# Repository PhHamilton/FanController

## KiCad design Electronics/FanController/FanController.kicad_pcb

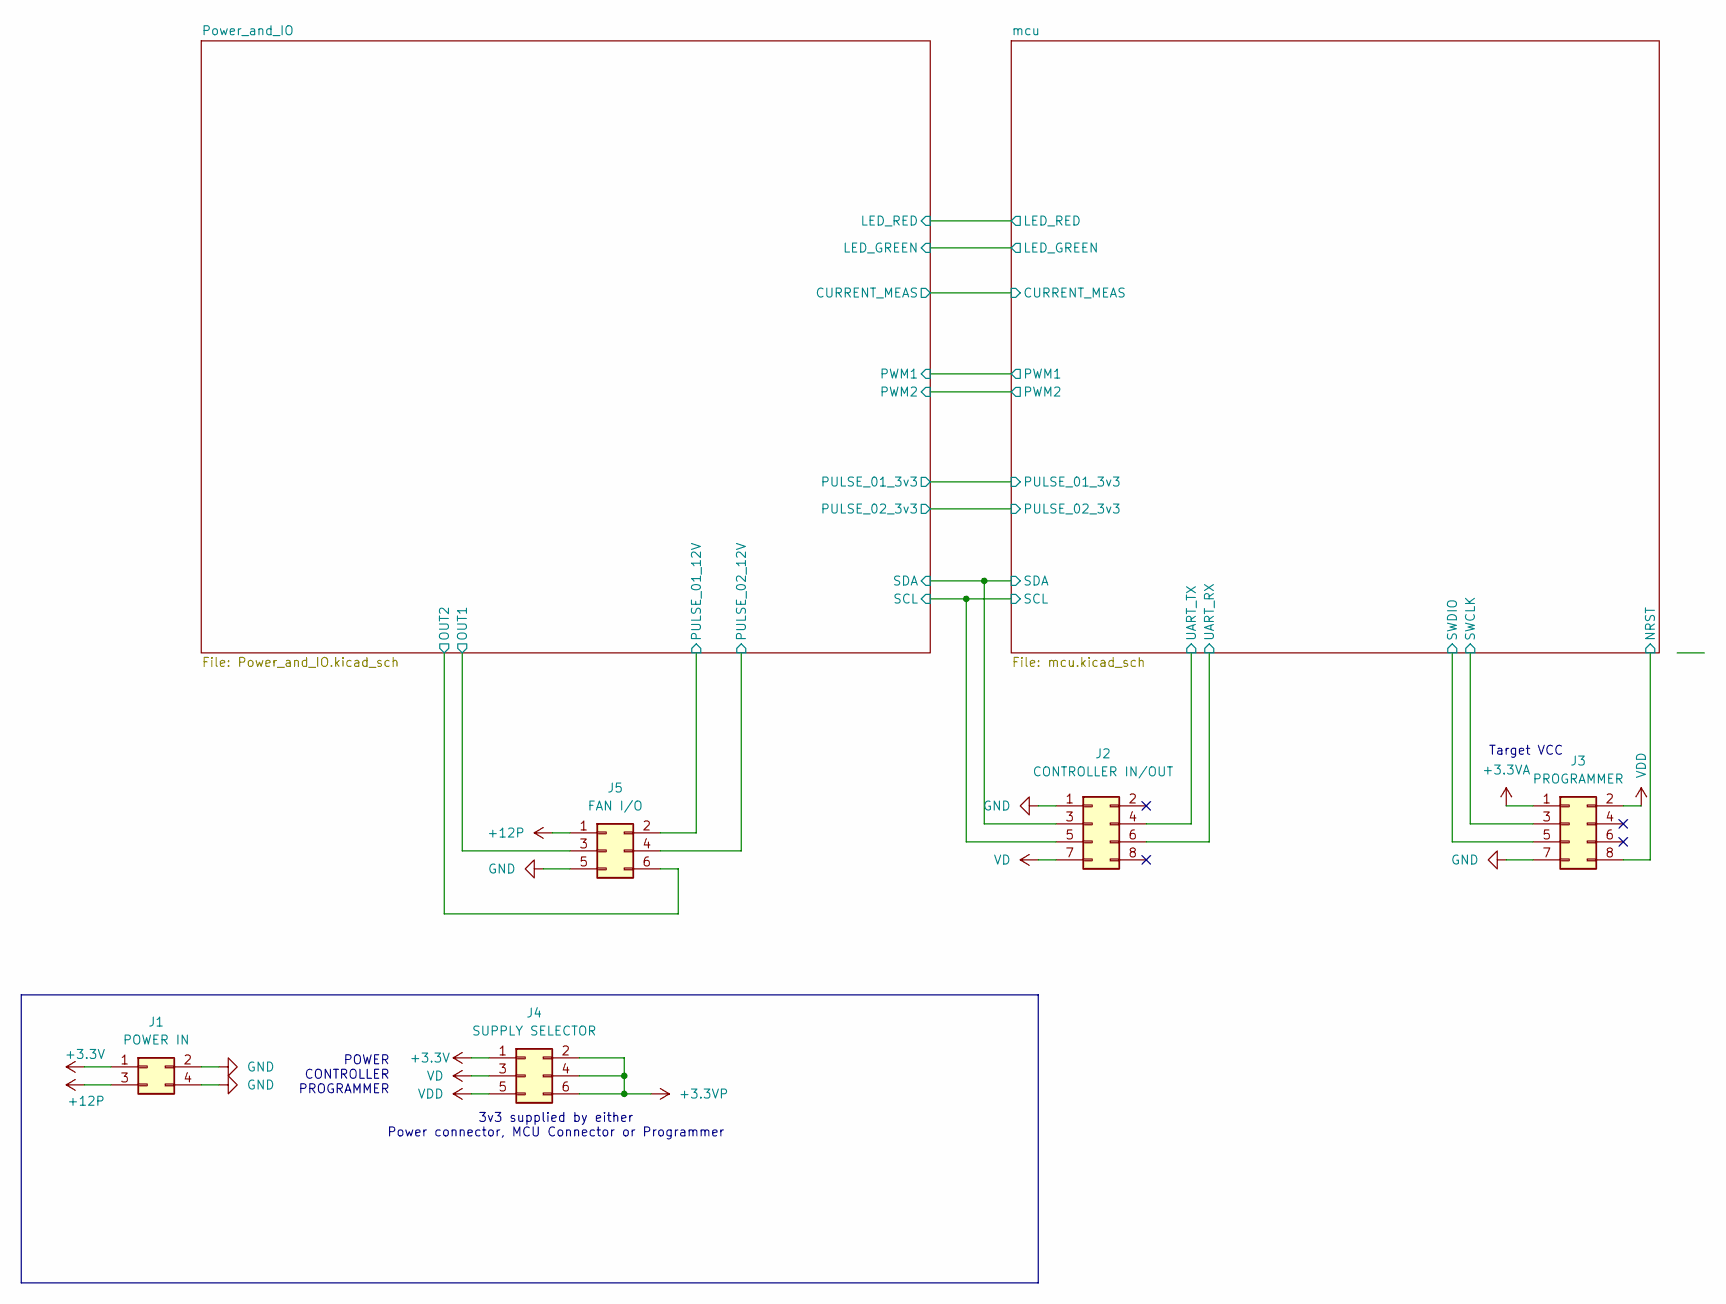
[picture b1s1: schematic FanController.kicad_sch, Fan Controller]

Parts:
J1: POWER IN; PinHeader_2x02_P2.54mm_Horizontal
J2: CONTROLLER IN/OUT; PinHeader_2x04_P2.54mm_Horizontal
J3: PROGRAMMER; PinHeader_2x04_P2.54mm_Vertical
J4: SUPPLY SELECTOR; PinHeader_2x03_P2.54mm_Vertical
J5: FAN I/O; PinHeader_2x03_P2.54mm_Horizontal

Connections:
+3.3V: J1.1, J4.1
+3.3VA: J3.1
+3.3VP: J4.2, J4.4, J4.6; also elsewhere on the board
+12P: J1.3, J5.1; also elsewhere on the board
/Power_and_IO/OUT1: J5.3; also elsewhere on the board
/Power_and_IO/OUT2: J5.6; also elsewhere on the board
/Power_and_IO/PULSE_01_12V: J5.2; also elsewhere on the board
/Power_and_IO/PULSE_02_12V: J5.4; also elsewhere on the board
/Power_and_IO/SCL: J2.5; also elsewhere on the board
/Power_and_IO/SDA: J2.3; also elsewhere on the board
/mcu/NRST: J3.8; also elsewhere on the board
/mcu/SWCLK: J3.3; also elsewhere on the board
/mcu/SWDIO: J3.5; also elsewhere on the board
/mcu/UART_RX: J2.6; also elsewhere on the board
/mcu/UART_TX: J2.4; also elsewhere on the board
GND: J1.2, J1.4, J2.1, J3.7, J5.5; also elsewhere on the board
VD: J2.7, J4.3
VDD: J3.2, J4.5

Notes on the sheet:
3v3 supplied by either Power connector, MCU Connector or Programmer
Target VCC
POWER CONTROLLER PROGRAMMER

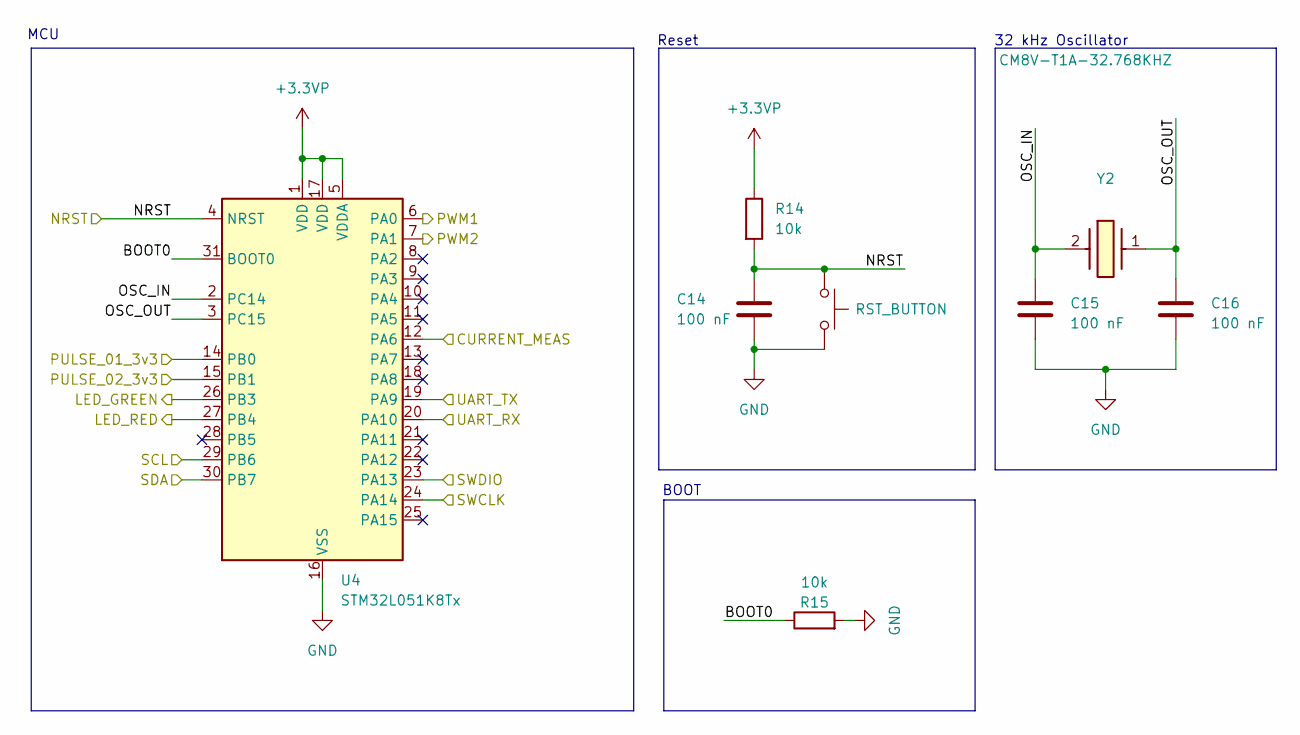
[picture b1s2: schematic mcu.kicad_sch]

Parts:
C14, C15, C16: 100 nF; C_1206_3216Metric_Pad1.33x1.80mm_HandSolder
R14, R15: 10k; R_1206_3216Metric_Pad1.30x1.75mm_HandSolder
SW1: RST_BUTTON; SW_Push_1P1T-SH_NO_CK_KMR2xxG
U4: STM32L051K8Tx; LQFP-32_7x7mm_P0.8mm
Y2: CM8V-T1A-32.768KHZ; Crystal_SMD_MicroCrystal_CC8V-T1A-2Pin_2.0x1.2mm_HandSolder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; Mouser Part Number 428-201494-MC01

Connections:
+3.3VP: R14.1, U4.1 (VDD), U4.5 (VDDA), U4.17 (VDD); also elsewhere on the board
/Power_and_IO/CURRENT_MEAS: U4.12 (PA6); also elsewhere on the board
/Power_and_IO/LED_GREEN: U4.26 (PB3); also elsewhere on the board
/Power_and_IO/LED_RED: U4.27 (PB4); also elsewhere on the board
/Power_and_IO/PULSE_01_3v3: U4.14 (PB0); also elsewhere on the board
/Power_and_IO/PULSE_02_3v3: U4.15 (PB1); also elsewhere on the board
/Power_and_IO/PWM1: U4.6 (PA0); also elsewhere on the board
/Power_and_IO/PWM2: U4.7 (PA1); also elsewhere on the board
/Power_and_IO/SCL: U4.29 (PB6); also elsewhere on the board
/Power_and_IO/SDA: U4.30 (PB7); also elsewhere on the board
/mcu/BOOT0: R15.1, U4.31 (BOOT0)
/mcu/NRST: C14.1, R14.2, SW1.1, U4.4 (NRST); also elsewhere on the board
/mcu/OSC_IN: C15.1, U4.2 (PC14), Y2.2 (X2)
/mcu/OSC_OUT: C16.1, U4.3 (PC15), Y2.1 (X1)
/mcu/SWCLK: U4.24 (PA14); also elsewhere on the board
/mcu/SWDIO: U4.23 (PA13); also elsewhere on the board
/mcu/UART_RX: U4.20 (PA10); also elsewhere on the board
/mcu/UART_TX: U4.19 (PA9); also elsewhere on the board
GND: C14.2, C15.2, C16.2, R15.2, SW1.2, U4.16 (VSS), U4.32 (VSS); also elsewhere on the board

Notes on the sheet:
32 kHz Oscillator
MCU
BOOT
Reset

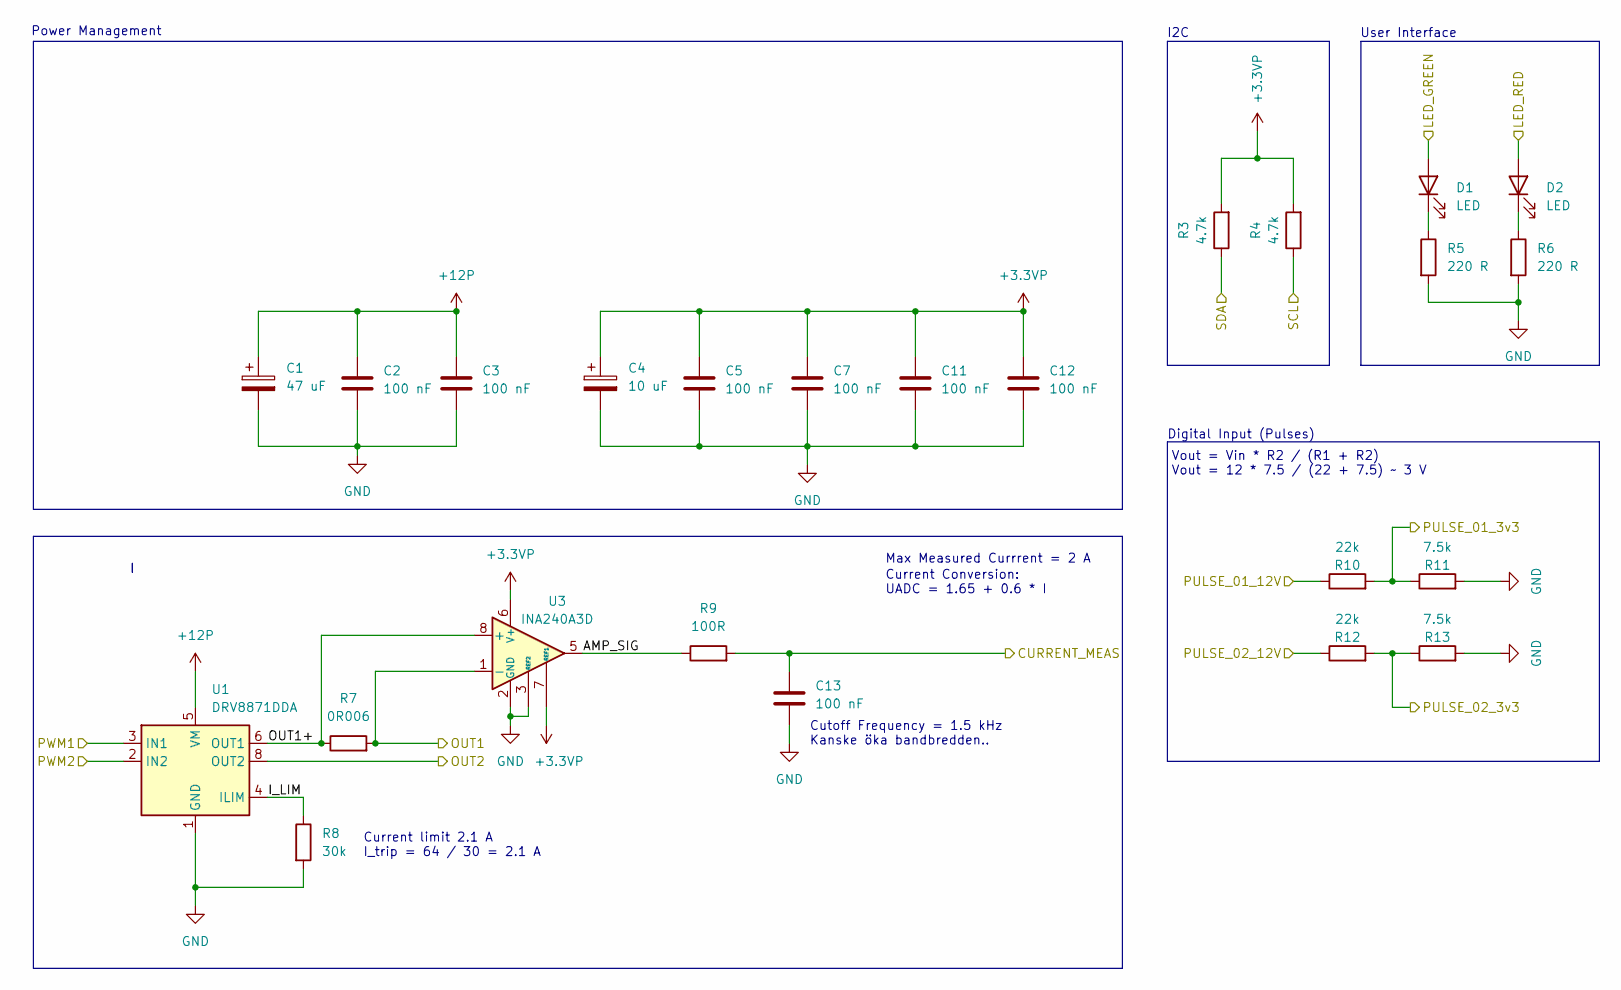
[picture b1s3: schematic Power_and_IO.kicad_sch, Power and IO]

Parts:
C1: 47 uF; C_Radial_D5.0mm_H5.0mm_P2.00mm
C2, C3, C5, C7, C11, C12, C13: 100 nF; C_1206_3216Metric_Pad1.33x1.80mm_HandSolder
C4: 10 uF; C_Radial_D5.0mm_H5.0mm_P2.00mm
D1, D2: LED; LED_1206_3216Metric_Pad1.42x1.75mm_HandSolder
R3, R4: 4.7k; R_1206_3216Metric_Pad1.30x1.75mm_HandSolder
R5, R6: 220 R; R_1206_3216Metric_Pad1.30x1.75mm_HandSolder
R7: 0R006; R_1206_3216Metric_Pad1.30x1.75mm_HandSolder
R8: 30k; R_1206_3216Metric_Pad1.30x1.75mm_HandSolder
R9: 100R; R_1206_3216Metric_Pad1.30x1.75mm_HandSolder
R10, R12: 22k; R_1206_3216Metric_Pad1.30x1.75mm_HandSolder
R11, R13: 7.5k; R_1206_3216Metric_Pad1.30x1.75mm_HandSolder
U1: DRV8871DDA; Texas_HTSOP-8-1EP_3.9x4.9mm_P1.27mm_EP2.95x4.9mm_Mask2.4x3.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
U3: INA240A3D; SOIC-8_3.9x4.9mm_P1.27mm

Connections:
+3.3VP: C4.1, C5.1, C7.1, C11.1, C12.1, R3.2, R4.2, U3.6 (V+), U3.7 (REF1); also elsewhere on the board
+12P: C1.1, C2.1, C3.1, U1.5 (VM); also elsewhere on the board
/Power_and_IO/AMP_SIG: R9.1, U3.5
/Power_and_IO/CURRENT_MEAS: C13.1, R9.2; also elsewhere on the board
/Power_and_IO/I_LIM: R8.1, U1.4 (ILIM)
/Power_and_IO/LED_GREEN: D1.2 (A); also elsewhere on the board
/Power_and_IO/LED_RED: D2.2 (A); also elsewhere on the board
/Power_and_IO/OUT1: R7.2, U3.1 (-); also elsewhere on the board
/Power_and_IO/OUT1+: R7.1, U1.6 (OUT1), U3.8 (+)
/Power_and_IO/OUT2: U1.8 (OUT2); also elsewhere on the board
/Power_and_IO/PULSE_01_3v3: R10.2, R11.1; also elsewhere on the board
/Power_and_IO/PULSE_01_12V: R10.1; also elsewhere on the board
/Power_and_IO/PULSE_02_3v3: R12.2, R13.1; also elsewhere on the board
/Power_and_IO/PULSE_02_12V: R12.1; also elsewhere on the board
/Power_and_IO/PWM1: U1.3 (IN1); also elsewhere on the board
/Power_and_IO/PWM2: U1.2 (IN2); also elsewhere on the board
/Power_and_IO/SCL: R4.1; also elsewhere on the board
/Power_and_IO/SDA: R3.1; also elsewhere on the board
GND: C1.2, C2.2, C3.2, C4.2, C5.2, C7.2, C11.2, C12.2, C13.2, R5.2, R6.2, R8.2, R11.2, R13.2, U1.1 (GND), U1.7 (GND), U1.9 (GND), U3.2 (GND), U3.3 (REF2), U3.4 (GND); also elsewhere on the board
unnamed: D1.1 (K), R5.1
unnamed: D2.1 (K), R6.1

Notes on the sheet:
Current Conversion: UADC = 1.65 + 0.6 * I
Vout = Vin * R2 / (R1 + R2) Vout = 12 * 7.5 / (22 + 7.5) ~ 3 V
Max Measured Currrent = 2 A
Digital Input (Pulses)
User Interface
Current limit 2.1 A I_trip = 64 / 30 = 2.1 A
Power Management
I2C
Cutoff Frequency = 1.5 kHz Kanske öka bandbredden..

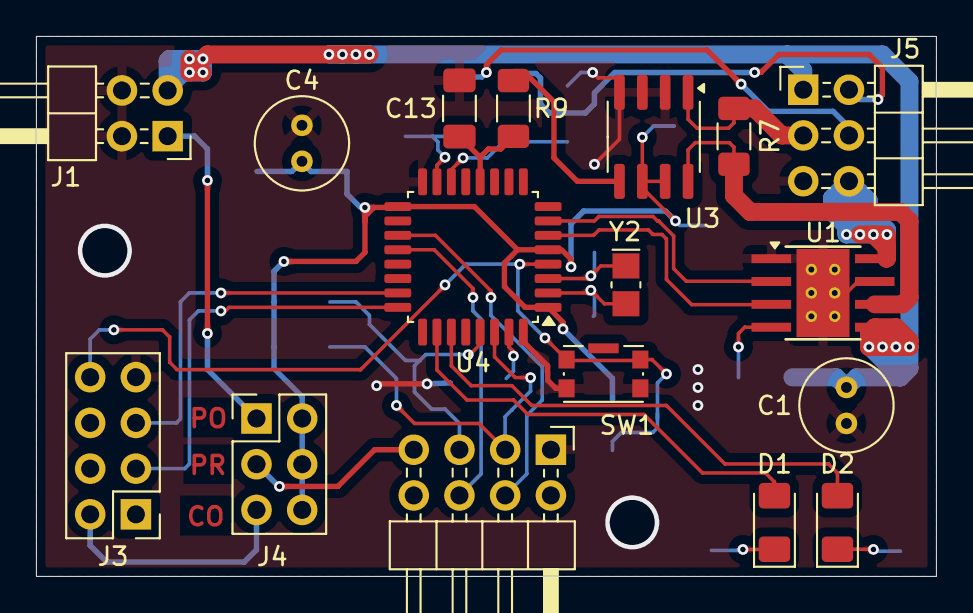
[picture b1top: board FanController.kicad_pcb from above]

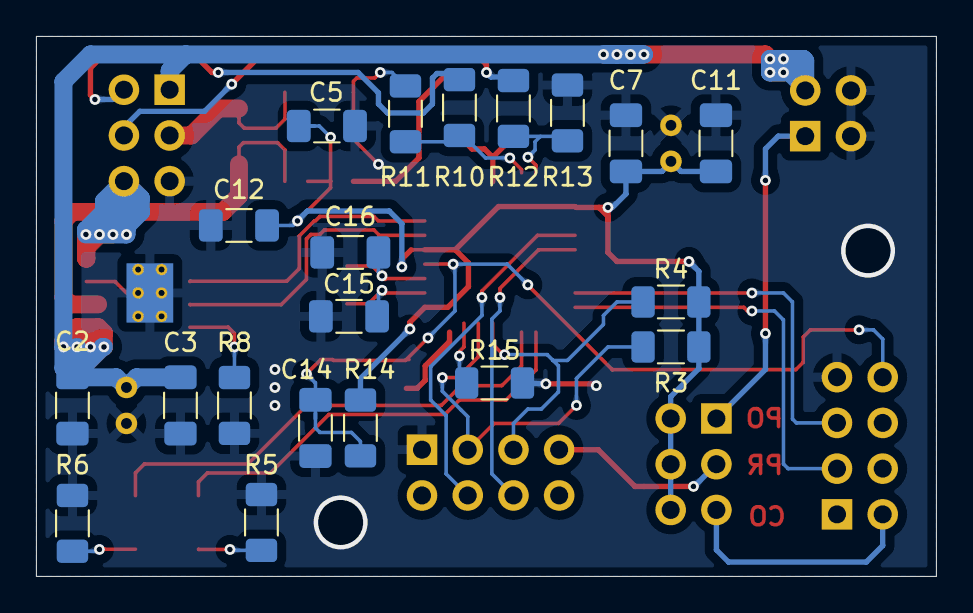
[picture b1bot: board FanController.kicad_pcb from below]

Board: 2 copper layers, 50.0 x 30.0 mm, 37 parts (20 on the bottom side), 32 nets.

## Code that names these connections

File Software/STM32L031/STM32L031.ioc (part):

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Mcu.Name=STM32L031K(4-6)Tx
Mcu.Package=LQFP32
Mcu.UserName=STM32L031K6Tx
PA0-CK_IN.GPIOParameters=GPIO_Label
PA0-CK_IN.GPIO_Label=PWM1
PA0-CK_IN.Signal=S_TIM2_CH1
PA1.GPIOParameters=GPIO_Label
PA1.GPIO_Label=PWM2
PA1.Signal=S_TIM2_CH2
PA10.GPIOParameters=GPIO_Label
PA10.GPIO_Label=UART_RX
PA10.Mode=Asynchronous
PA10.Signal=USART2_RX
PA13.Mode=Serial_Wire
PA13.Signal=SYS_SWDIO
PA14.Mode=Serial_Wire
PA14.Signal=SYS_SWCLK
PA6.GPIOParameters=GPIO_Label
PA6.GPIO_Label=CURRENT_MEAS
PA6.Mode=IN6
PA6.Signal=ADC_IN6
PA9.GPIOParameters=GPIO_Label
PA9.GPIO_Label=UART_TX
PA9.Mode=Asynchronous
PA9.Signal=USART2_TX
PB0.GPIOParameters=GPIO_Label
PB0.GPIO_Label=PULSE_01_3v3
PB0.Signal=GPIO_Input
PB1.GPIOParameters=GPIO_Label
PB1.GPIO_Label=PULSE_02_3v3
PB1.Signal=GPIO_Input
PB3.GPIOParameters=GPIO_Label
PB3.GPIO_Label=LED_GREEN
PB3.Signal=GPIO_Output
PB4.GPIOParameters=GPIO_Label
PB4.GPIO_Label=LED_RED
PB4.Signal=GPIO_Output
PB6.Mode=I2C
PB6.Signal=I2C1_SCL
PB7.Mode=I2C
PB7.Signal=I2C1_SDA
PC14-OSC32_IN.Mode=LSE-External-Oscillator
PC14-OSC32_IN.Signal=RCC_OSC32_IN
PC15-OSC32_OUT.Mode=LSE-External-Oscillator
PC15-OSC32_OUT.Signal=RCC_OSC32_OUT
RCC.HSE_VALUE=8000000
RCC.SYSCLKFreq_VALUE=32000000
RCC.SYSCLKSource=RCC_SYSCLKSOURCE_PLLCLK
board=custom

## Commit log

2025-01-06 Started on the schematics
2025-01-06 Added headers
2025-01-07 Added current measurement and reverse polarity protection
2025-01-13 Updated schematic
2025-01-13 Added blank SW
2025-01-13 Updated user labels
2025-01-19 Started PCB-routing
2025-01-20 Changed schematic
2025-01-20 Removed lock
2025-01-23 Routed PCB-layout
2025-01-27 Finished routing
2025-02-01 Updated .gitignore with vim and .zip files
2025-02-01 Added ADC and LED Handler, changed IOC to PWM 10 KHz, ADC 4 MHz
2025-02-01 Finialized Circuitboard
2025-02-10 Updated with new code for STM32L031
2025-02-10 New files generated due to new controller
2025-02-10 removing deleted files from tracking
2025-02-10 Added step file for controller
2025-02-10 Removed .lck
